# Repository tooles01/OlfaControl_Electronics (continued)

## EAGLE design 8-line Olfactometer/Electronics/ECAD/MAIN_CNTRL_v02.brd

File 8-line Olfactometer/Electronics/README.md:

# 8-line Olfactometer

## PCB Assembly
- Attach (x2) heat sinks to VR1 and VR2 using (x2) 4-40 x 1/4" screw and hex nut
- Solder Arduino header pins onto PCB
- Set I2C address on S1 (full dictionary of addresses is currently stored in master.ino source code)
- Connect master Arduino
    - Make a wire to connect from J2 (4pos Molex female) to master Arduino pins (Dupont male wires). Connect to SDA, SCL, GND and GND.
    - (Mount master Arduino on top using Arduino holder 3D printed part)

<br><br><br>

## updates for version 2:

### power:
- single 24V power supply (instead of 1x 24V supply and 1x 10V supply)
    - voltage regulators & corresponding circuitry to shift down to 10V for the components that need it
    - (2 voltage regulators + heat sinks to prevent overheating when multiple lines activated at once)

### error fixes:
- fixes (x4) incorrectly wired proportional valves
- removes connection between isolation valves 3 & 8

### other:
- multiple boards can be chained together by a single ribbon cable, which carries the power and I2C lines
    - (only 1 board in the chain needs a 24V input, the rest receive power through the ribbon cable)
- updated header for connecting to mixing chamber (standard 10pos IDC cable)

### new components:
- (x8) LEDs to indicate isolation valve activated
- (x2) LEDs to indicate power (10V, 24V)
- (x1) connection for additional flow sensor
- (x1) connection for additional proportional valve
- (x2) connection for additional isolation valve
- (x1) connection for Alicat MFC

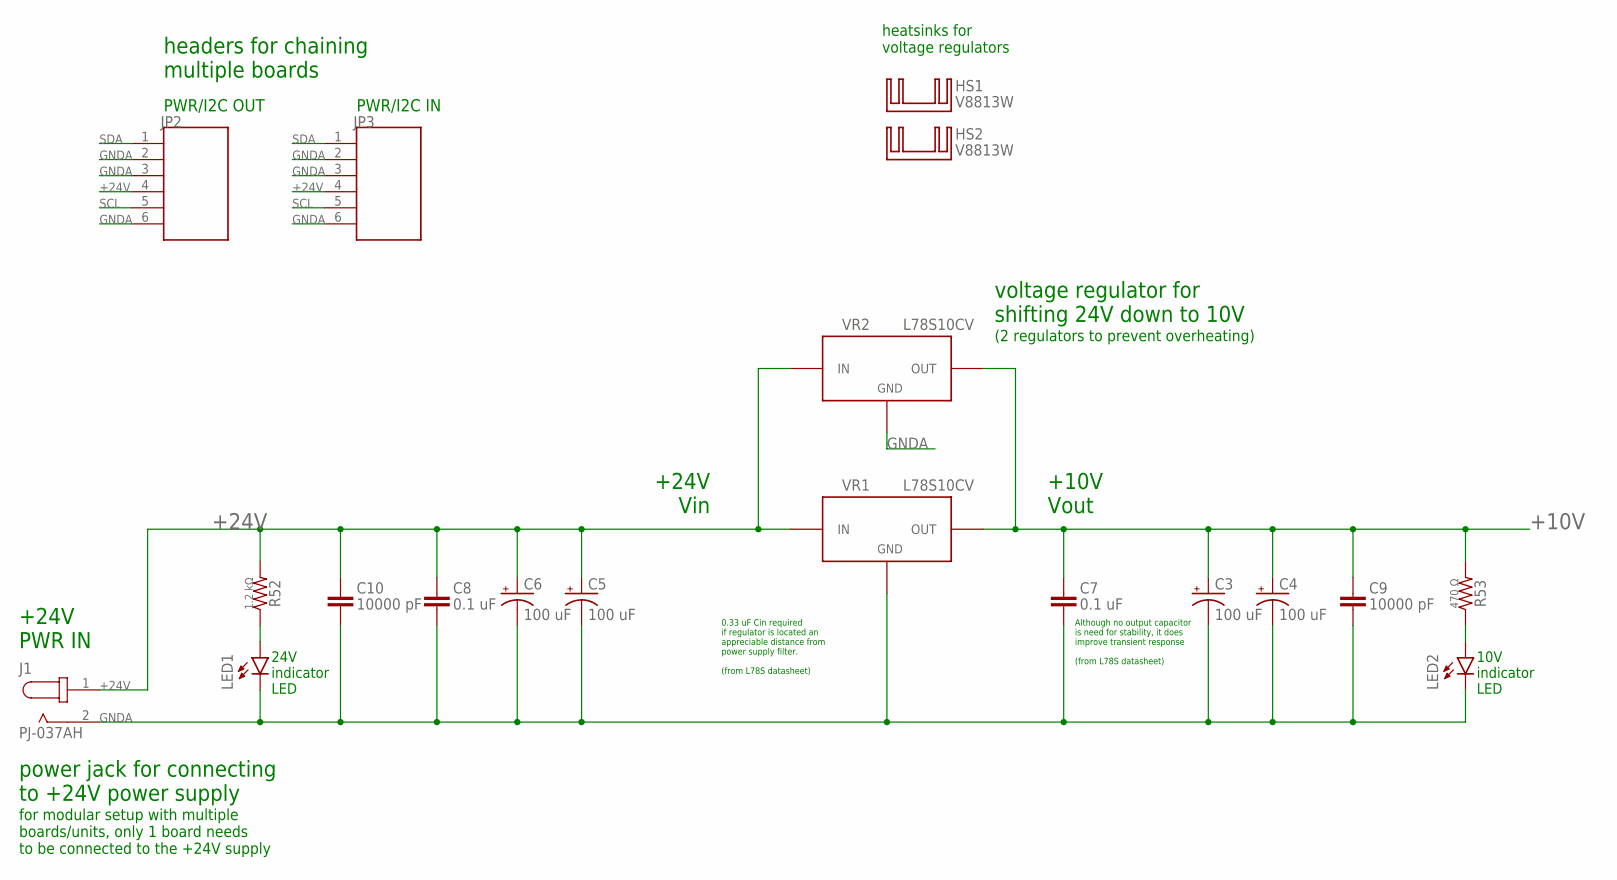
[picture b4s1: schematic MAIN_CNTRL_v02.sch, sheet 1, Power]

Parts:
C3, C4, C5, C6: 100 uF; CAP_J-V_10X10P5_RUB
C7, C8: 0.1 uF; CAP_1608_TDK
C9, C10: 10000 pF; CAP_1608_TDK
HS1, HS2: V8813W; V8813X
J1: PJ-037AH; CUI_PJ-037AH
JP2, JP3: CONN_06_HEADER; CONN_6P_TE_1761681-1
LED1, LED2: Green LED; LED_VISHAY_VLMX13XX
R52: 1.2 kΩ; RCS0603_REFLOW
R53: 470 Ω; RCS0603_REFLOW
VR1, VR2: L78S10CV

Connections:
+10V: C3.+, C4.+, C7.1, C9.1, R53.2, VR1.3 (OUT), VR2.3 (OUT); also elsewhere on the board
+24V: C5.+, C6.+, C8.1, C10.1, J1.1, JP2.4, JP3.4, R52.2, VR1.1 (IN), VR2.1 (IN); also elsewhere on the board
GNDA: C3.-, C4.-, C5.-, C6.-, C7.2, C8.2, C9.2, C10.2, J1.2, JP2.2, JP2.3, JP2.6, JP3.2, JP3.3, JP3.6, LED1.C, LED2.C, VR1.2 (GND), VR2.2 (GND); also elsewhere on the board
unnamed: LED1.A, R52.1
unnamed: LED2.A, R53.1
SCL: JP2.5, JP3.5; also elsewhere on the board
SDA: JP2.1, JP3.1; also elsewhere on the board

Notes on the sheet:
voltage regulator for shifting 24V down to 10V
+24V Vin
+10V Vout
power jack for connecting to +24V power supply
PWR/I2C IN
24V indicator LED
10V indicator LED
PWR/I2C OUT
+24V PWR IN
for modular setup with multiple boards/units, only 1 board needs to be connected to the +24V supply
Although no output capacitor is need for stability, it does improve transient response (from L78S datasheet)
headers for chaining multiple boards
0.33 uF Cin required if regulator is located an appreciable distance from power supply filter. (from L78S datasheet)
(2 regulators to prevent overheating)
heatsinks for voltage regulators

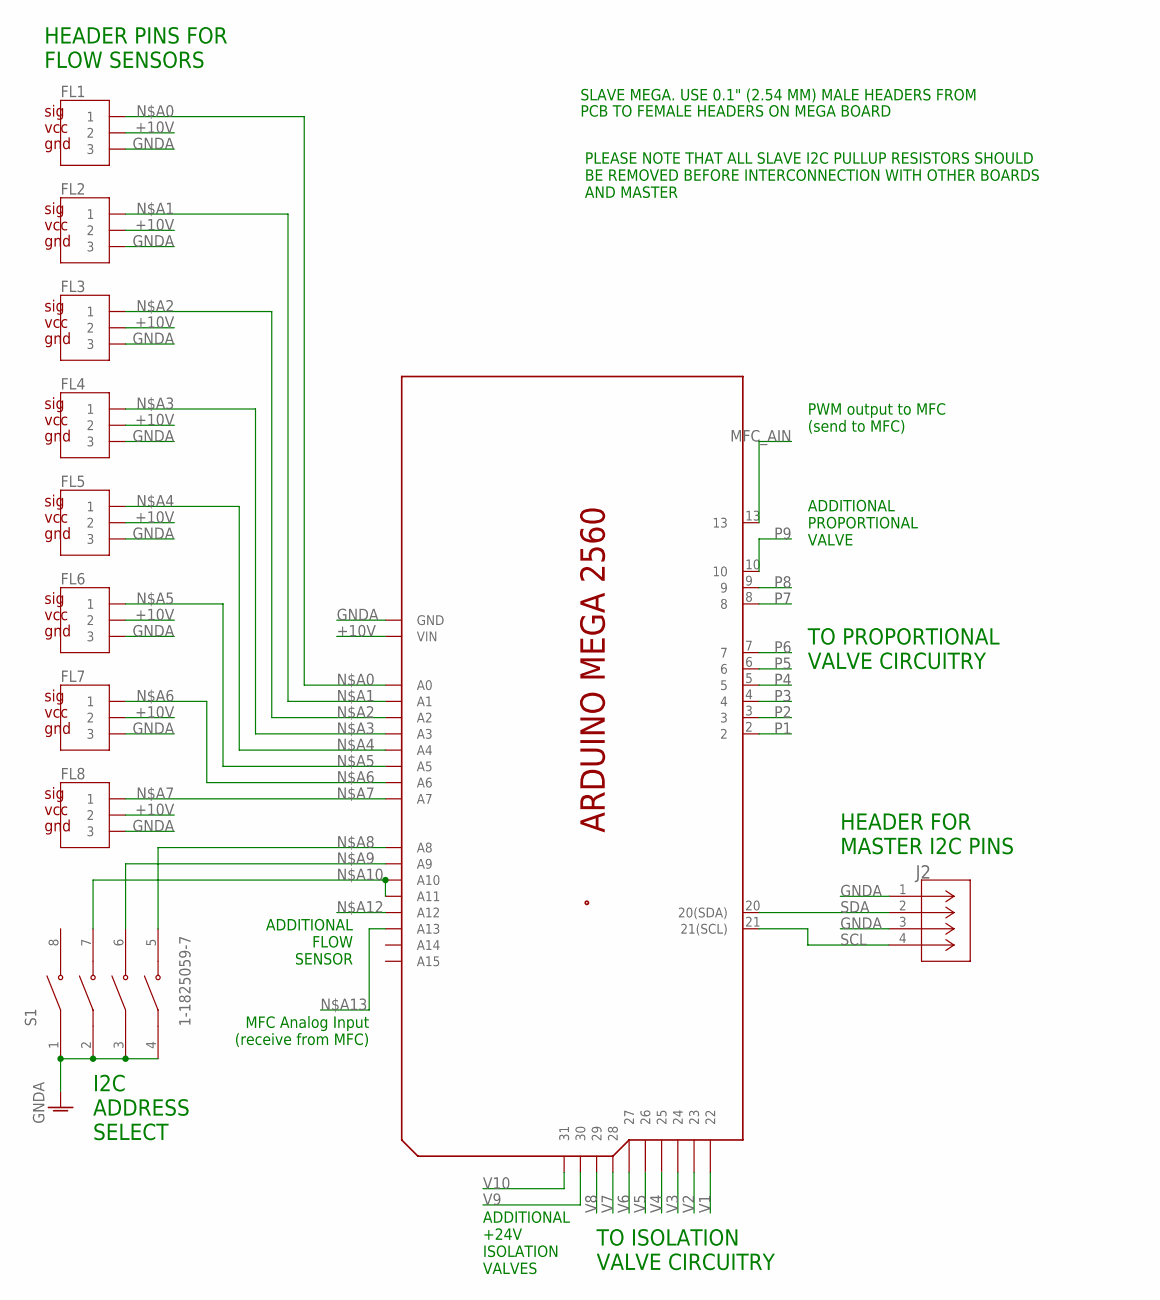
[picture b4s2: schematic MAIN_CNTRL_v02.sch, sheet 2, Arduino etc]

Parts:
FL1, FL2, FL3, FL4, FL5, FL6, FL7, FL8: CONN_03_FL; 1X03_FL
J2: MOLEX_436500415; MOLEX_4P_FOOTPRINT
S1: 1-1825059-7; SW_1-1825059-7
X1: ARDUINO_MEGA2560_HEADERPINSXX; ARDUINO_MEGA2560_ST_FLIPPED_CUTS

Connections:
+10V: FL1.2, FL2.2, FL3.2, FL4.2, FL5.2, FL6.2, FL7.2, FL8.2, X1.VIN; also elsewhere on the board
GNDA: FL1.3, FL2.3, FL3.3, FL4.3, FL5.3, FL6.3, FL7.3, FL8.3, J2.1, J2.3, S1.1, S1.2, S1.3, S1.4, X1.GND, X1.GND. (GND), X1.GND.. (GND); also elsewhere on the board
MFC_AIN: X1.13; also elsewhere on the board
N$A0: FL1.1, X1.A0
N$A1: FL2.1, X1.A1
N$A2: FL3.1, X1.A2
N$A3: FL4.1, X1.A3
N$A4: FL5.1, X1.A4
N$A5: FL6.1, X1.A5
N$A6: FL7.1, X1.A6
N$A7: FL8.1, X1.A7
N$A8: S1.5, X1.A8
N$A9: S1.6, X1.A9
N$A10: S1.7, X1.A10, X1.A11
N$A12: X1.A12; also elsewhere on the board
N$A13: X1.A13; also elsewhere on the board
P1: X1.2; also elsewhere on the board
P2: X1.3; also elsewhere on the board
P3: X1.4; also elsewhere on the board
P4: X1.5; also elsewhere on the board
P5: X1.6; also elsewhere on the board
P6: X1.7; also elsewhere on the board
P7: X1.8; also elsewhere on the board
P8: X1.9; also elsewhere on the board
P9: X1.10; also elsewhere on the board
SCL: J2.4, X1.21 (21(SCL)); also elsewhere on the board
SDA: J2.2, X1.20 (20(SDA)); also elsewhere on the board
V1: X1.22; also elsewhere on the board
V2: X1.23; also elsewhere on the board
V3: X1.24; also elsewhere on the board
V4: X1.25; also elsewhere on the board
V5: X1.26; also elsewhere on the board
V6: X1.27; also elsewhere on the board
V7: X1.28; also elsewhere on the board
V8: X1.29; also elsewhere on the board
V9: X1.30; also elsewhere on the board
V10: X1.31; also elsewhere on the board

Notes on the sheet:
I2C ADDRESS SELECT
SLAVE MEGA. USE 0.1" (2.54 MM) MALE HEADERS FROM
PCB TO FEMALE HEADERS ON MEGA BOARD
HEADER FOR MASTER I2C PINS
PLEASE NOTE THAT ALL SLAVE I2C PULLUP RESISTORS SHOULD BE REMOVED BEFORE INTERCONNECTION WITH OTHER BOARDS AND MASTER
HEADER PINS FOR FLOW SENSORS
TO PROPORTIONAL VALVE CIRCUITRY
TO ISOLATION VALVE CIRCUITRY
ADDITIONAL FLOW SENSOR
ADDITIONAL +24V ISOLATION VALVES
ADDITIONAL PROPORTIONAL VALVE
MFC Analog Input (receive from MFC)
PWM output to MFC (send to MFC)

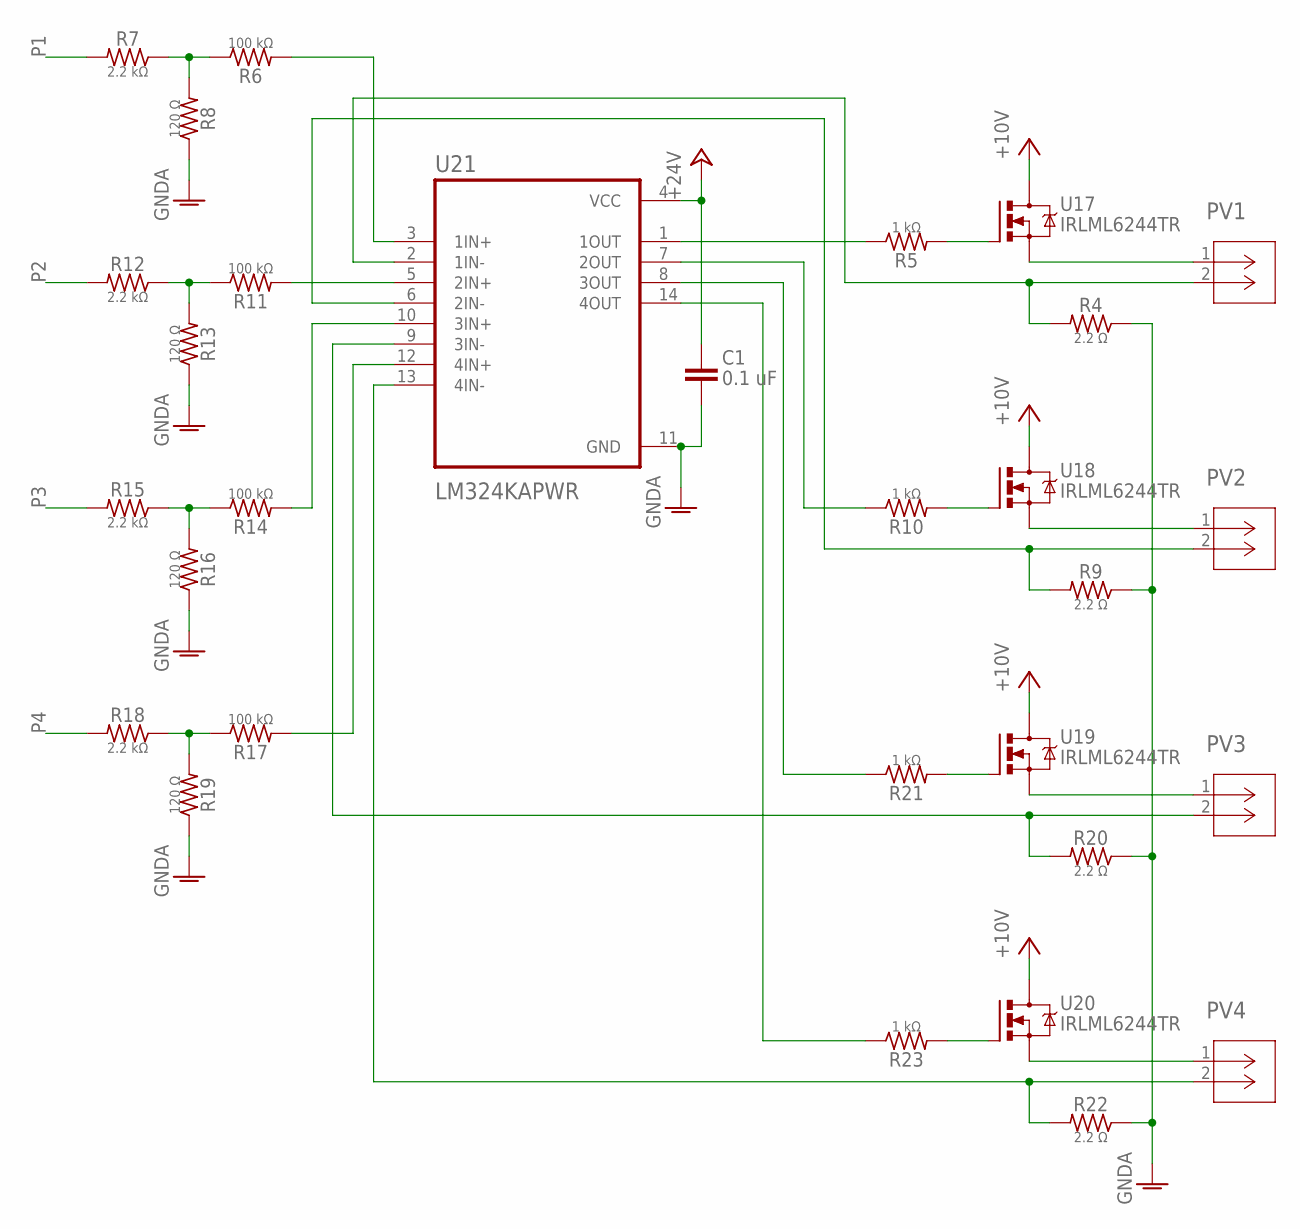
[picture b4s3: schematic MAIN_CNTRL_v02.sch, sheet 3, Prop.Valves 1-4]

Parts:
C1: 0.1 uF; CAP_1608_TDK
PV1, PV2, PV3, PV4: MOLEX_436500215PVALVES; MOLEX_2P_PVALVES
R4, R9, R20, R22: 2.2 Ω; CRCW1206_E3_REFLOW
R5, R10, R21, R23: 1 kΩ; RES_ERJPA3F1001V
R6, R11, R14, R17: 100 kΩ; RESC1608X55N
R7, R12, R15, R18: 2.2 kΩ; RESC1608X55N
R8, R13, R16, R19: 120 Ω; RCS0603_REFLOW
U17, U18, U19, U20: IRLML6244TR; SOT23
U21: LM324KAPWR; SOP65P640X120-14N

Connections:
+10V: U17.3 (D), U18.3 (D), U19.3 (D), U20.3 (D); also elsewhere on the board
+24V: C1.1, U21.4 (VCC); also elsewhere on the board
GNDA: C1.2, R4.1, R8.1, R9.1, R13.1, R16.1, R19.1, R20.1, R22.1, U21.11 (GND); also elsewhere on the board
unnamed: R6.1, R7.1, R8.2
unnamed: R6.2, U21.3 (1IN+)
unnamed: R5.2, U17.1 (G)
unnamed: R11.1, R12.1, R13.2
unnamed: R11.2, U21.5 (2IN+)
unnamed: R10.2, U18.1 (G)
unnamed: R14.1, R15.1, R16.2
unnamed: R14.2, U21.10 (3IN+)
unnamed: R21.2, U19.1 (G)
unnamed: R17.1, R18.1, R19.2
unnamed: R17.2, U21.12 (4IN+)
unnamed: R23.2, U20.1 (G)
N$PV1_1: PV1.1, U17.2 (S)
N$PV1_2: PV1.2, R4.2, U21.2 (1IN-)
N$PV1_OUT: R5.1, U21.1 (1OUT)
N$PV2_1: PV2.1, U18.2 (S)
N$PV2_2: PV2.2, R9.2, U21.6 (2IN-)
N$PV2_OUT: R10.1, U21.7 (2OUT)
N$PV3_1: PV3.1, U19.2 (S)
N$PV3_2: PV3.2, R20.2, U21.9 (3IN-)
N$PV3_OUT: R21.1, U21.8 (3OUT)
N$PV4_1: PV4.1, U20.2 (S)
N$PV4_2: PV4.2, R22.2, U21.13 (4IN-)
N$PV4_OUT: R23.1, U21.14 (4OUT)
P1: R7.2; also elsewhere on the board
P2: R12.2; also elsewhere on the board
P3: R15.2; also elsewhere on the board
P4: R18.2; also elsewhere on the board

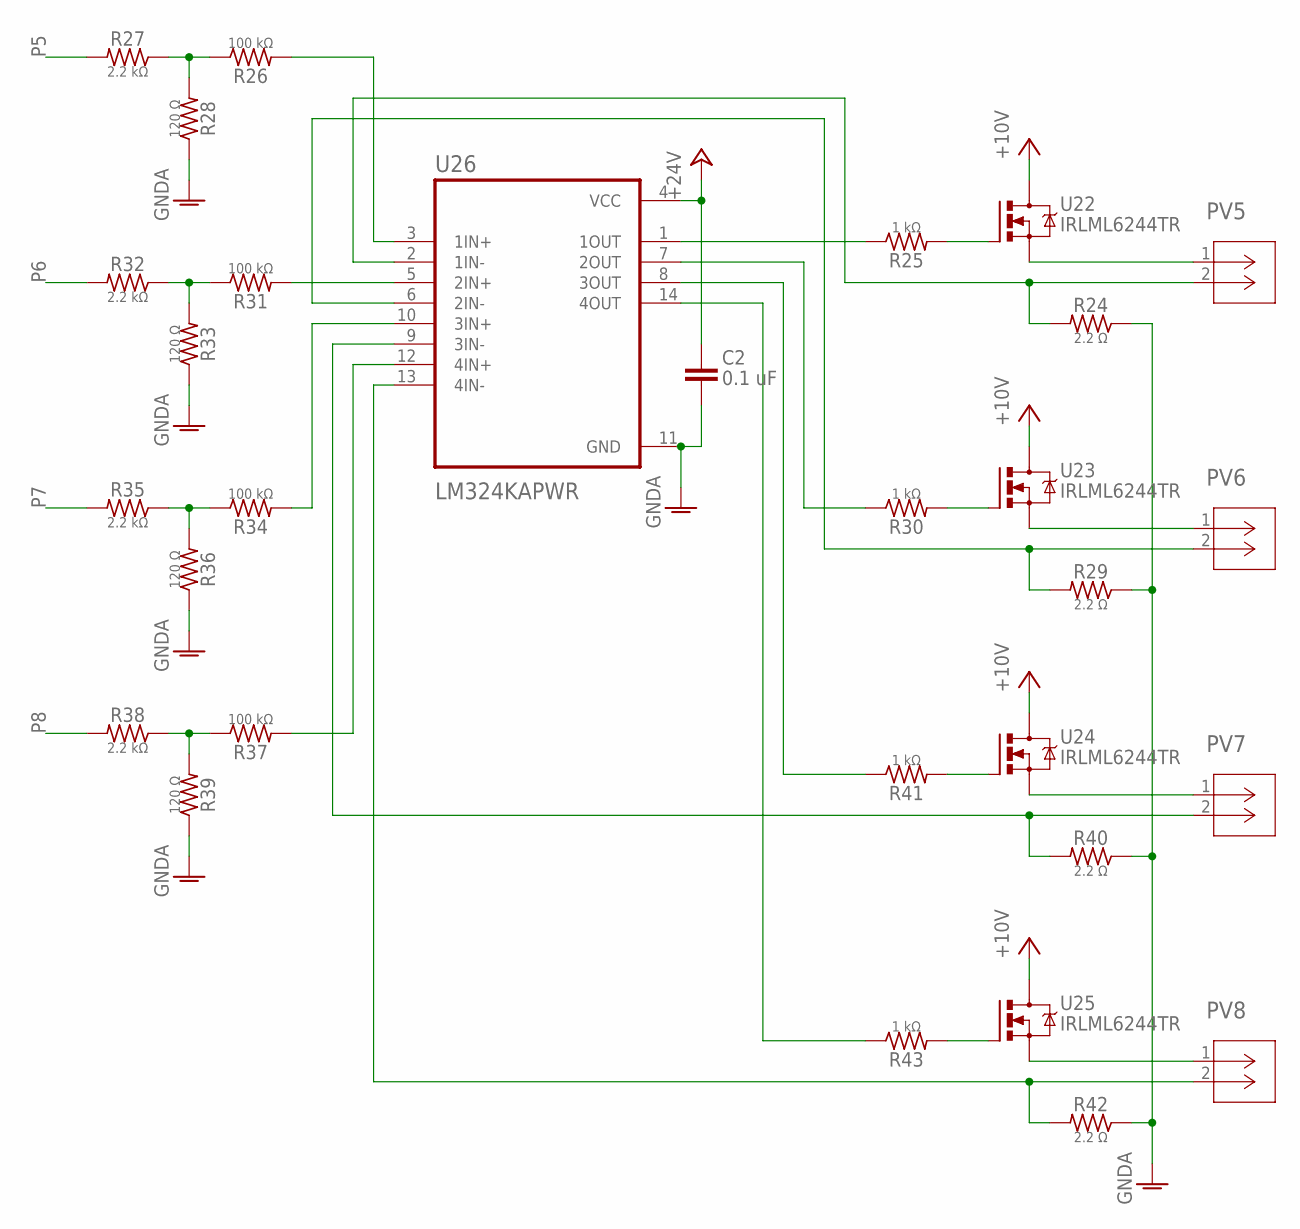
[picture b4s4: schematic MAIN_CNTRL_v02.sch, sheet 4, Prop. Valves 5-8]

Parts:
C2: 0.1 uF; CAP_1608_TDK
PV5, PV6, PV7, PV8: MOLEX_436500215PVALVES; MOLEX_2P_PVALVES
R24, R29, R40, R42: 2.2 Ω; CRCW1206_E3_REFLOW
R25, R30, R41, R43: 1 kΩ; RES_ERJPA3F1001V
R26, R31, R34, R37: 100 kΩ; RESC1608X55N
R27, R32, R35, R38: 2.2 kΩ; RESC1608X55N
R28, R33, R36, R39: 120 Ω; RCS0603_REFLOW
U22, U23, U24, U25: IRLML6244TR; SOT23
U26: LM324KAPWR; SOP65P640X120-14N

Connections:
+10V: U22.3 (D), U23.3 (D), U24.3 (D), U25.3 (D); also elsewhere on the board
+24V: C2.1, U26.4 (VCC); also elsewhere on the board
GNDA: C2.2, R24.1, R28.1, R29.1, R33.1, R36.1, R39.1, R40.1, R42.1, U26.11 (GND); also elsewhere on the board
unnamed: R26.1, R27.1, R28.2
unnamed: R26.2, U26.3 (1IN+)
unnamed: R25.2, U22.1 (G)
unnamed: R31.1, R32.1, R33.2
unnamed: R31.2, U26.5 (2IN+)
unnamed: R30.2, U23.1 (G)
unnamed: R34.1, R35.1, R36.2
unnamed: R34.2, U26.10 (3IN+)
unnamed: R41.2, U24.1 (G)
unnamed: R37.1, R38.1, R39.2
unnamed: R37.2, U26.12 (4IN+)
unnamed: R43.2, U25.1 (G)
N$PV5_1: PV5.1, U22.2 (S)
N$PV5_2: PV5.2, R24.2, U26.2 (1IN-)
N$PV5_OUT: R25.1, U26.1 (1OUT)
N$PV6_1: PV6.1, U23.2 (S)
N$PV6_2: PV6.2, R29.2, U26.6 (2IN-)
N$PV6_OUT: R30.1, U26.7 (2OUT)
N$PV7_1: PV7.1, U24.2 (S)
N$PV7_2: PV7.2, R40.2, U26.9 (3IN-)
N$PV7_OUT: R41.1, U26.8 (3OUT)
N$PV8_1: PV8.1, U25.2 (S)
N$PV8_2: PV8.2, R42.2, U26.13 (4IN-)
N$PV8_OUT: R43.1, U26.14 (4OUT)
P5: R27.2; also elsewhere on the board
P6: R32.2; also elsewhere on the board
P7: R35.2; also elsewhere on the board
P8: R38.2; also elsewhere on the board

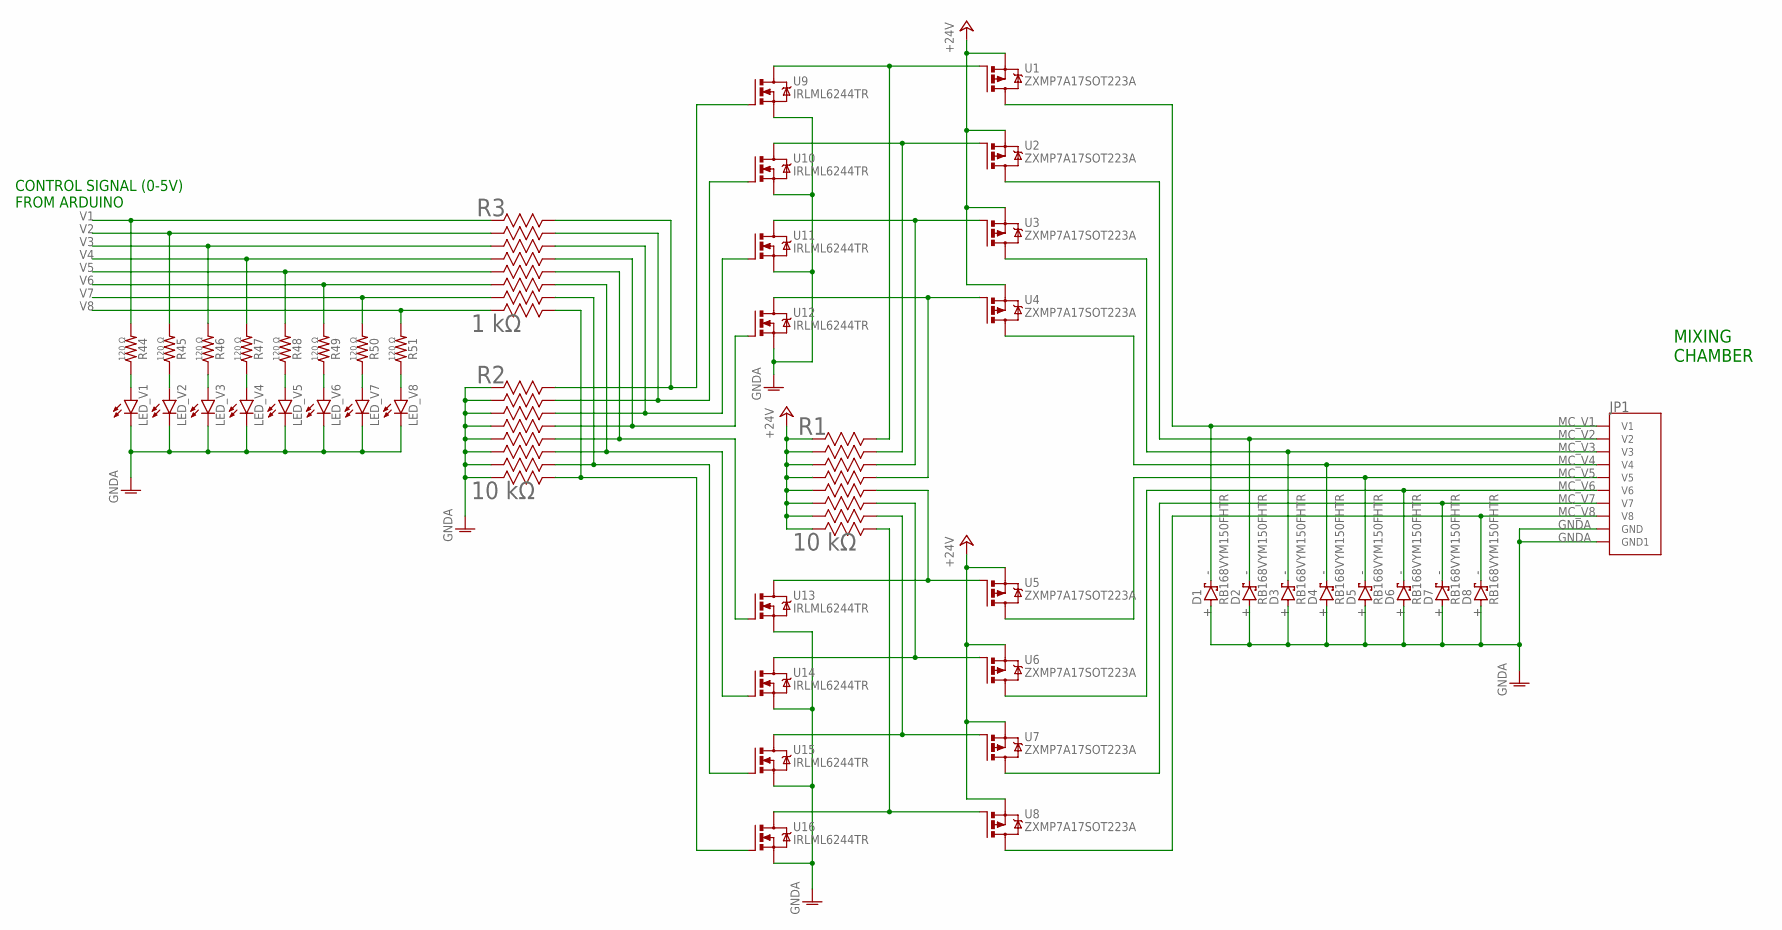
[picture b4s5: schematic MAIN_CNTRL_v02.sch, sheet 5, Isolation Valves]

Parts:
D1, D2, D3, D4, D5, D6, D7, D8: RB168VYM150FHTR; DIO_RB160VAM_ROM
JP1: CONN_10P_CUSTOM_N2510-6002RBV02; CONN_10P_TE_1761681-3_SE_FOR_V02
LED_V1, LED_V2, LED_V3, LED_V4, LED_V5, LED_V6, LED_V7, LED_V8: Blue LED; LED_VISHAY_VLMX13XX
R1, R2: 10 kΩ; BO_4816P
R3: 1 kΩ; BO_4816P
R44, R45, R46, R47, R48, R49, R50, R51: 120 Ω; RCS0603_REFLOW
U1, U2, U3, U4, U5, U6, U7, U8: ZXMP7A17SOT223A; SOT223
U9, U10, U11, U12, U13, U14, U15, U16: IRLML6244TR; SOT23

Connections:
+24V: R1.1, R1.2, R1.3, R1.4, R1.5, R1.6, R1.7, R1.8, U1.3 (S), U2.3 (S), U3.3 (S), U4.3 (S), U5.3 (S), U6.3 (S), U7.3 (S), U8.3 (S); also elsewhere on the board
GNDA: D1.2 (A), D2.2 (A), D3.2 (A), D4.2 (A), D5.2 (A), D6.2 (A), D7.2 (A), D8.2 (A), JP1.GND, JP1.GND. (GND1), LED_V1.C, LED_V2.C, LED_V3.C, LED_V4.C, LED_V5.C, LED_V6.C, LED_V7.C, LED_V8.C, R2.1, R2.2, R2.3, R2.4, R2.5, R2.6, R2.7, R2.8, U9.2 (S), U10.2 (S), U11.2 (S), U12.2 (S), U13.2 (S), U14.2 (S), U15.2 (S), U16.2 (S); also elsewhere on the board
MC_V1: D1.1 (C), JP1.V1, U1.2 (D), U1.4 (D)
MC_V2: D2.1 (C), JP1.V2, U2.2 (D), U2.4 (D)
MC_V3: D3.1 (C), JP1.V3, U3.2 (D), U3.4 (D)
MC_V4: D4.1 (C), JP1.V4, U4.2 (D), U4.4 (D)
MC_V5: D5.1 (C), JP1.V5, U5.2 (D), U5.4 (D)
MC_V6: D6.1 (C), JP1.V6, U6.2 (D), U6.4 (D)
MC_V7: D7.1 (C), JP1.V7, U7.2 (D), U7.4 (D)
MC_V8: D8.1 (C), JP1.V8, U8.2 (D), U8.4 (D)
unnamed: R1.16, U1.1 (G), U9.3 (D)
unnamed: R2.16, R3.16, U9.1 (G)
unnamed: R1.15, U2.1 (G), U10.3 (D)
unnamed: R2.15, R3.15, U10.1 (G)
unnamed: R1.14, U3.1 (G), U11.3 (D)
unnamed: R2.14, R3.14, U11.1 (G)
unnamed: R1.13, U4.1 (G), U12.3 (D)
unnamed: R2.13, R3.13, U12.1 (G)
unnamed: R1.12, U5.1 (G), U13.3 (D)
unnamed: R2.12, R3.12, U13.1 (G)
unnamed: R1.11, U6.1 (G), U14.3 (D)
unnamed: R2.11, R3.11, U14.1 (G)
unnamed: R1.10, U7.1 (G), U15.3 (D)
unnamed: R2.10, R3.10, U15.1 (G)
unnamed: R1.9, U8.1 (G), U16.3 (D)
unnamed: R2.9, R3.9, U16.1 (G)
N$LED1: LED_V1.A, R44.1
N$LED2: LED_V2.A, R45.1
N$LED3: LED_V3.A, R46.1
N$LED4: LED_V4.A, R47.1
N$LED5: LED_V5.A, R48.1
N$LED6: LED_V6.A, R49.1
N$LED7: LED_V7.A, R50.1
N$LED8: LED_V8.A, R51.1
V1: R3.1, R44.2; also elsewhere on the board
V2: R3.2, R45.2; also elsewhere on the board
V3: R3.3, R46.2; also elsewhere on the board
V4: R3.4, R47.2; also elsewhere on the board
V5: R3.5, R48.2; also elsewhere on the board
V6: R3.6, R49.2; also elsewhere on the board
V7: R3.7, R50.2; also elsewhere on the board
V8: R3.8, R51.2; also elsewhere on the board

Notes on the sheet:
MIXING CHAMBER
CONTROL SIGNAL (0-5V) FROM ARDUINO

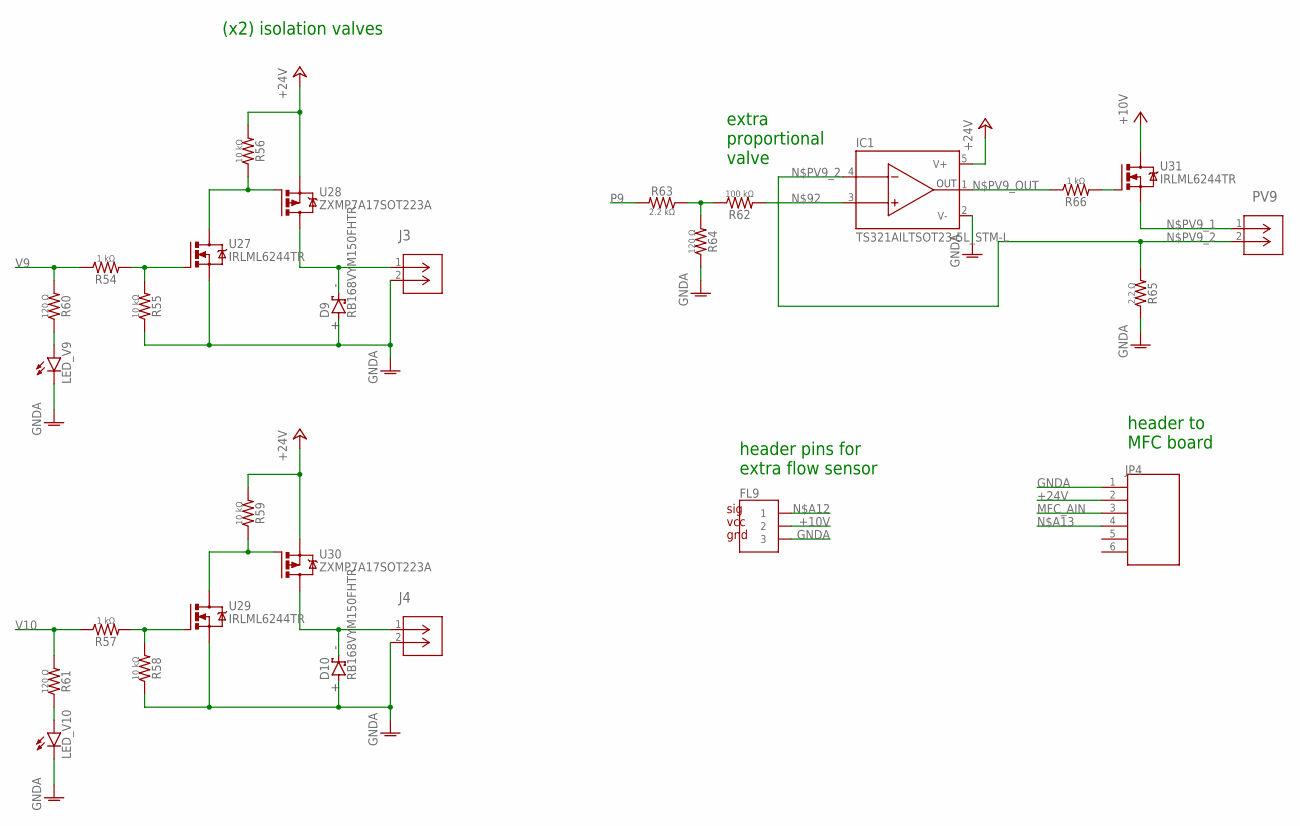
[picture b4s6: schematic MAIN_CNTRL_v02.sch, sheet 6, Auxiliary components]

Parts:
D9, D10: RB168VYM150FHTR; DIO_RB160VAM_ROM
FL9: CONN_03_FL; 1X03_FL
IC1: TS321AILTSOT23-5L_STM-L; SOT23-5L_STM-L
J3, J4: MOLEX_436500215; MOLEX_2P_FOOTPRINT
JP4: CONN_06_HEADER; CONN_6P_TE_1761681-1
LED_V9, LED_V10: Blue LED; LED_VISHAY_VLMX13XX
PV9: MOLEX_436500215PVALVES; MOLEX_2P_PVALVES
R54, R57, R66: 1 kΩ; RES_ERJPA3F1001V
R55, R56, R58, R59: 10 kΩ; RES_ERJPA3F1001V
R60, R61, R64: 120 Ω; RCS0603_REFLOW
R62: 100 kΩ; RESC1608X55N
R63: 2.2 kΩ; RESC1608X55N
R65: 2.2 Ω; CRCW1206_E3_REFLOW
U27, U29, U31: IRLML6244TR; SOT23
U28, U30: ZXMP7A17SOT223A; SOT223

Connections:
+10V: FL9.2, U31.3 (D); also elsewhere on the board
+24V: IC1.5 (V+), JP4.2, R56.2, R59.2, U28.3 (S), U30.3 (S); also elsewhere on the board
GNDA: D9.2 (A), D10.2 (A), FL9.3, IC1.2 (V-), J3.2, J4.2, JP4.1, LED_V9.C, LED_V10.C, R55.1, R58.1, R64.1, R65.1, U27.2 (S), U29.2 (S); also elsewhere on the board
MFC_AIN: JP4.3; also elsewhere on the board
unnamed: R56.1, U27.3 (D), U28.1 (G)
unnamed: R54.2, R55.2, U27.1 (G)
unnamed: R59.1, U29.3 (D), U30.1 (G)
unnamed: R57.2, R58.2, U29.1 (G)
unnamed: R62.1, R63.1, R64.2
unnamed: IC1.3 (+IN), R62.2
unnamed: R66.2, U31.1 (G)
N$A12: FL9.1; also elsewhere on the board
N$A13: JP4.4; also elsewhere on the board
N$LED9: LED_V9.A, R60.1
N$LED10: LED_V10.A, R61.1
N$PV9_1: PV9.1, U31.2 (S)
N$PV9_2: IC1.4 (-IN), PV9.2, R65.2
N$PV9_OUT: IC1.1 (OUT), R66.1
N$V9: D9.1 (C), J3.1, U28.2 (D), U28.4 (D)
N$V10: D10.1 (C), J4.1, U30.2 (D), U30.4 (D)
P9: R63.2; also elsewhere on the board
V9: R54.1, R60.2; also elsewhere on the board
V10: R57.1, R61.2; also elsewhere on the board

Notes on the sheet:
header pins for extra flow sensor
(x2) isolation valves
extra proportional valve
header to MFC board

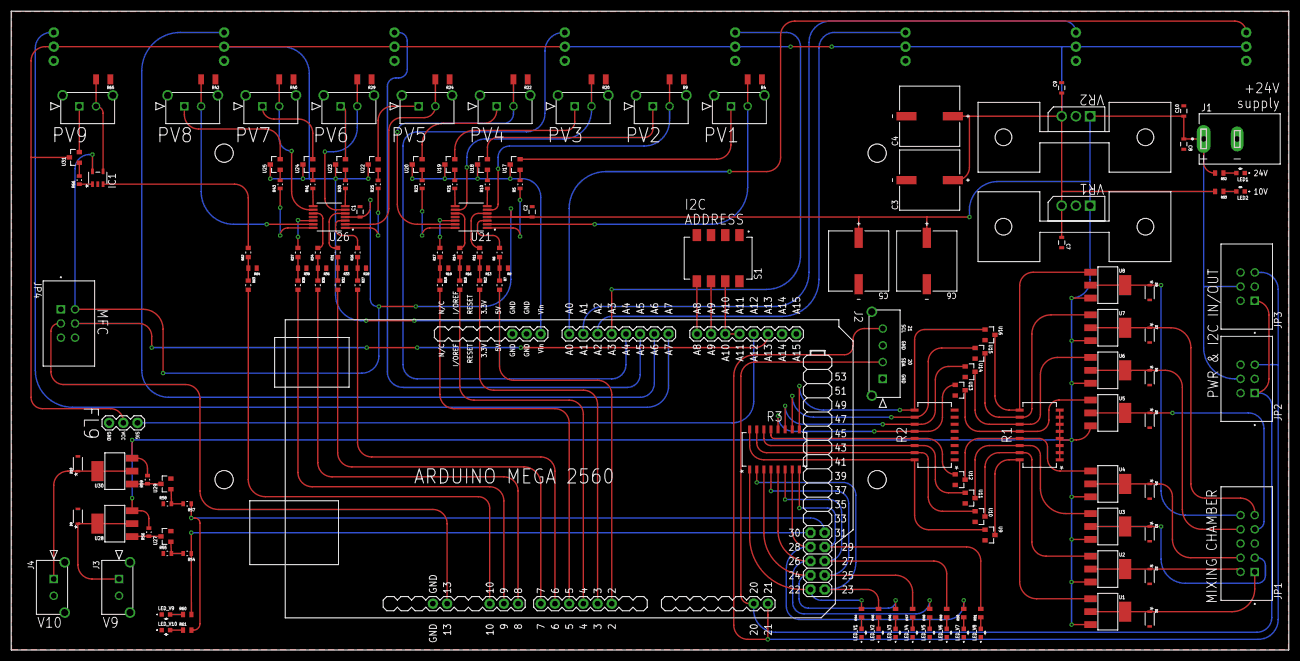
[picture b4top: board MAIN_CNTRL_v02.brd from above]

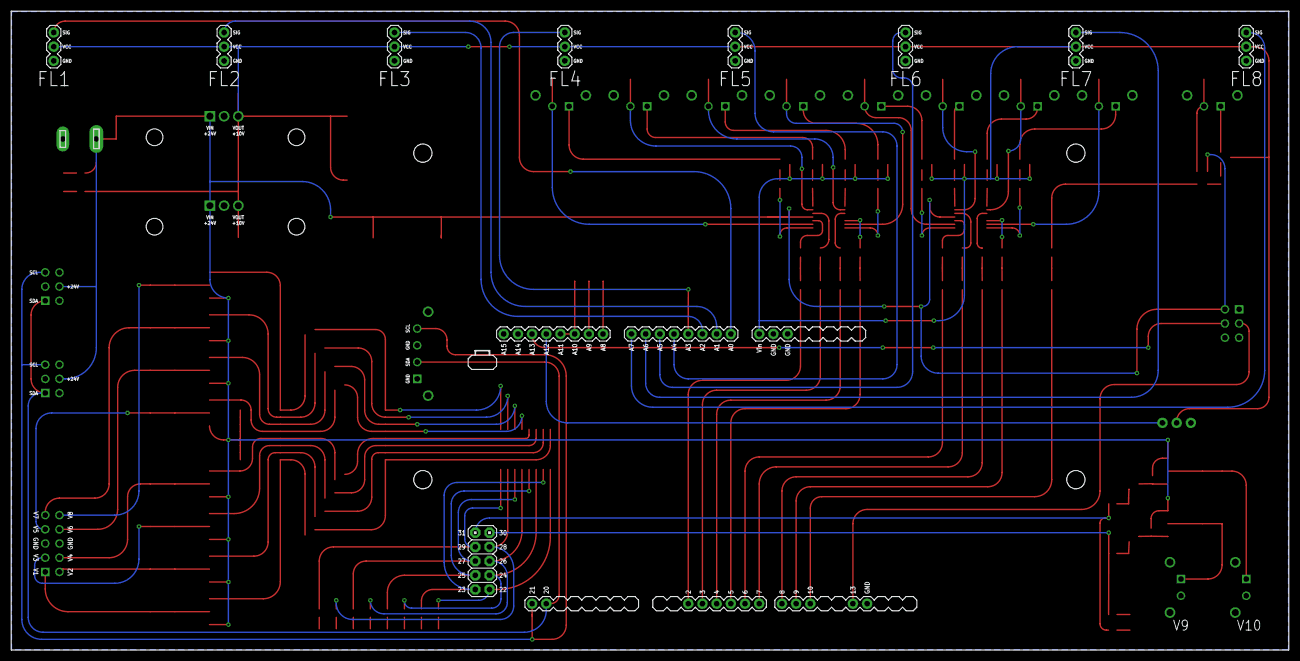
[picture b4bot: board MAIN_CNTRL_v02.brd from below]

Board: 2 copper layers, 228.6 x 114.3 mm, 162 parts (8 on the bottom side), 134 nets.

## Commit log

2023-03-15 Create README.md
    initial commit
2023-03-15 removed duplicate files
2023-03-29 initial commit - names of files in Fusion
2023-04-11 renamed folder
2023-04-11 updated to version 2
2023-04-11 renamed image files
2023-04-11 initial commit - BOM for MAIN_CNTRL v01
2023-04-12 initial commit: 3D PCB with silkscreen
2023-04-12 folder relocation
2023-04-14 initial commit - hardware files for v01
2023-04-18 created separate Electronics folder
2023-04-18 moved 3D PCB files to Electronics folder
2023-04-18 folder reorg
2023-04-18 initial commit - .ipt files for hardware
2023-04-18 renamed v01 .ipt files
2023-05-04 initial commit of hardware readme
2023-05-08 fixed incorrectly uploaded pdf of brd file
2023-05-08 reorganized mixing chamber directories; separated Lee and Clippard designs into differed directories
2023-05-09 initial upload of Clippard 8-MC Electronics files
2023-05-09 renamed Clippard 8-MC image file
2023-05-09 initial upload of README for Clippard 8-MC electronics
2023-05-09 fixed image link in Clippard Electronics readme
2023-05-09 Lee 8-MC readme
2023-05-09 initial commit of Lee 8-MC Electronics files for manufacturing
2023-05-09 upload of Clippard & Lee BOMs
2023-05-18 upload of 3D PCB readme & accompanying image
2023-05-18 trying to get image to show up in 3D PCB readme
2023-05-18 add image to 8-line Olfa Electronics readme
2023-05-18 renamed 3D PCB image
2023-05-18 added 3D PCB image to Olfa Electronics readme
2023-05-18 fixed error in olfa 3D PCB image
2023-05-18 uploaded 8-line olfa hardware images
2023-06-14 initial commit of full system images
2023-06-15 initial commit of olfa schemetics
2023-06-15 renamed images
2023-06-15 initial commit of README (draft, with images)
2023-08-29 initial commit of 8-line Olfactometer images
2023-10-03 initial commit of Arduino holder
2023-10-03 initial commit
    10-24 nut for Clippard 8-MC (v01)
2023-11-20 initial commit - first draft of Clippard assembly instructions
2023-11-20 initial commit - first draft of olfactometer assembly instructions
2023-11-28 Add files via upload
    initial commit of vialHolder files
2023-11-29 Add files via upload
    initial commit of mainPlate
2023-11-29 Add files via upload
    initial commit of full assembly image
2023-12-09 folder organization
2023-12-09 image update
2023-12-09 Upload README.md
2024-01-05 Updated mount_bracket parts
2024-01-26 Clippard 8-MC heart: fixed previously uploaded incorrect drawing
2024-01-26 3D printed parts: initial commit of Arduino holder & vialHolder
2024-01-26 Olfa 3D printed parts: initial commit of new mount parts, organization of various mounting parts within folder
2024-01-26 Olfa manufacturing: restore files that were accidentally deleted on previous folder reorg (12/11/23)
2024-01-26 Olfa manufacturing: folder reorg
2024-01-26 Clippard MC: folder reorg
2024-01-26 Olfa: Updated readme to include a troubleshooting section
2024-02-27 Clippard 8-MC: initial commit of .ipt CAD files
2024-02-27 Clippard 8-MC: recreated .ipt CAD files in Inventor
2024-03-11 Olfa assembly instructions: test upload for inserting pictures into document
2024-03-11 Olfa assembly instructions: updates for clarity
2024-03-12 Olfa: test upload of flow calibration protocol
2024-03-18 Olfa 3D printed parts: updated version of vialHolder
    Adds stabilizing piece under main plate
2024-03-18 Olfa Assembly Instructions: further updates with images
2024-03-18 Olfactometer: Updates to README
2024-03-21 Mixing Chamber: initial commit of README for output fitting
2024-03-21 Mixing Chamber: update to README for output fitting
2024-03-21 Olfa: reorganized folder
2024-03-21 Clippard MC: reorganized folder
2024-03-22 Mixing Chamber: uploaded hardware & PCB images, 3D PCB files
2024-03-22 Mixing Chamber: reorg
2024-03-22 Mixing Chamber: image upload
2024-03-22 Mixing Chamber: fix to error in Electronics readme
2024-03-22 Mixing Chamber: ACTUAL fix to error in Electronics readme
    previous commit was update to Olfactometer\Electronics readme (added PCB assembly instructions)
2024-03-22 Mixing Chamber: updated to correct versions of v01 .ipt files
2024-04-09 Updated README to include actual image of setup
2024-05-13 Olfactometer: renamed images
2024-05-13 Clippard 8-MC: added README (+ images)
    and reorganized folder a little
2024-05-13 Clippard 8-MC hardware updated to version 2
2024-05-13 Moved remaining Clippard 8-MC v01 files to separate folder
2024-06-14 removed duplicate schematics
2024-06-14 Updated flow sensor calibration protocol
2024-06-14 inital commit of olfactometer BOM draft
2024-06-18 Fix to flow sensor calibration protocol example calibration table image
2024-06-21 Updated README schematics: Full System Schematic_simplified
2024-06-21 Reorganized Mixing Chamber directory
2024-06-21 Moved Mixing Chamber schematics from main directory to Mixing Chamber folder
2024-06-21 Moved Olfactometer schematics from main directory to Olfactometer directory
2024-06-21 initial commit of full system schematic
2024-06-26 Minor updates to air flow schematics
    Main schematic now includes Alicat MFC & needle valve
2024-07-13 Updated flow sensor calibration protocol
    Now includes instructions for calibrating while flow sensors installed on olfa manifold
2024-07-13 Updated flow sensor calibration protocol
    Minor formatting edits
2024-07-16 Updates to Flow Sensor Calibration Protocol
    Added example config file (for updating once calibration is complete)
    Added some clarifying details to protocol
2024-07-16 Updated Flow Sensor Calibration Protocol
    Formatting edits
2024-07-16 Updated README
    Added labeled image of complete system
2024-07-23 Minor updates to schematic (Added labels for clean/mixed air + other slight adjustments)
    (Updated from v06 to v08)
2024-08-05 Minor updates to Full System Schematic
    Updated to v09
2024-08-08 Updated olfa_full image
    larger label text
2024-08-23 Updated olfa assembly instructions: added images of vial holder assembly
    also some minor formatting edits
2024-08-29 Updated Troubleshooting section in olfactometer README
    Reformatted & added further potential issues
2024-09-03 Updated Mixing Chamber assembly instructions
    Added images for connecting cover to heart
2024-09-03 Updated Olfactometer assembly instructions
    Added images for assembling vial holders & PCB
2024-09-03 Formatting updates to flow sensor calibration protocol
2024-09-17 Updated Flow Sensor Calibration schematic
    Moved calibration images to separate folder; minor formatting updates to calibration protocol
2024-09-17 Updated Full System Schematic
2024-09-27 Updated MC assembly instructions: Added images for attaching PCB to cover
2024-09-28 Updated MC README
    - Added section on changes from v1 to v2
    - Added manufacturing details
2024-10-14 Updated Olfactometer BOM
2024-10-15 Flow Sensor Calibration Protocol: minor clarifying edits & schematic update
2024-10-29 Added images for Lee 8-MC
2024-11-19 Updated image names
2024-11-19 Upload draft of disassembly instructions
2024-11-19 Upload of Clippard 8-MC BOM
2024-12-20 Reorganized Olfactometer Hardware directories
2024-12-28 Test: initial commit of Read the Docs config file
2025-05-07 Olfa PCB BOM: renamed to v02
2025-05-09 Minor assembly instruction updates (to clear git queue)
2025-05-09 General organization
    MC: Moved ECAD to its own folder, committed non-changes to hardware files (to clear git queue)
    Olfactometer: Committed non-changes to 3D PCB (to clear git queue)
2025-05-13 Olfa 3D printed parts: Updated vialHolder (slightly shorter, larger cutout for fitting tubing through)
2025-05-13 Olfa: Cleaned 3D printed parts folder
2025-05-13 Updated olfa README (reformatted troubleshooting section)
2025-05-15 Olfa: Updated documentation for mounting components
    Added images of setup types, temporarily removed the CAD files for the 'sliding only' parts
2025-10-06 Renamed ECAD for clarity
2026-06-25 Updated .sch pdf to Fusion formatting for easier future comparisons
2026-06-25 Updated .brd pdf to standard Eagle output formatting (for easier future comparisons)
